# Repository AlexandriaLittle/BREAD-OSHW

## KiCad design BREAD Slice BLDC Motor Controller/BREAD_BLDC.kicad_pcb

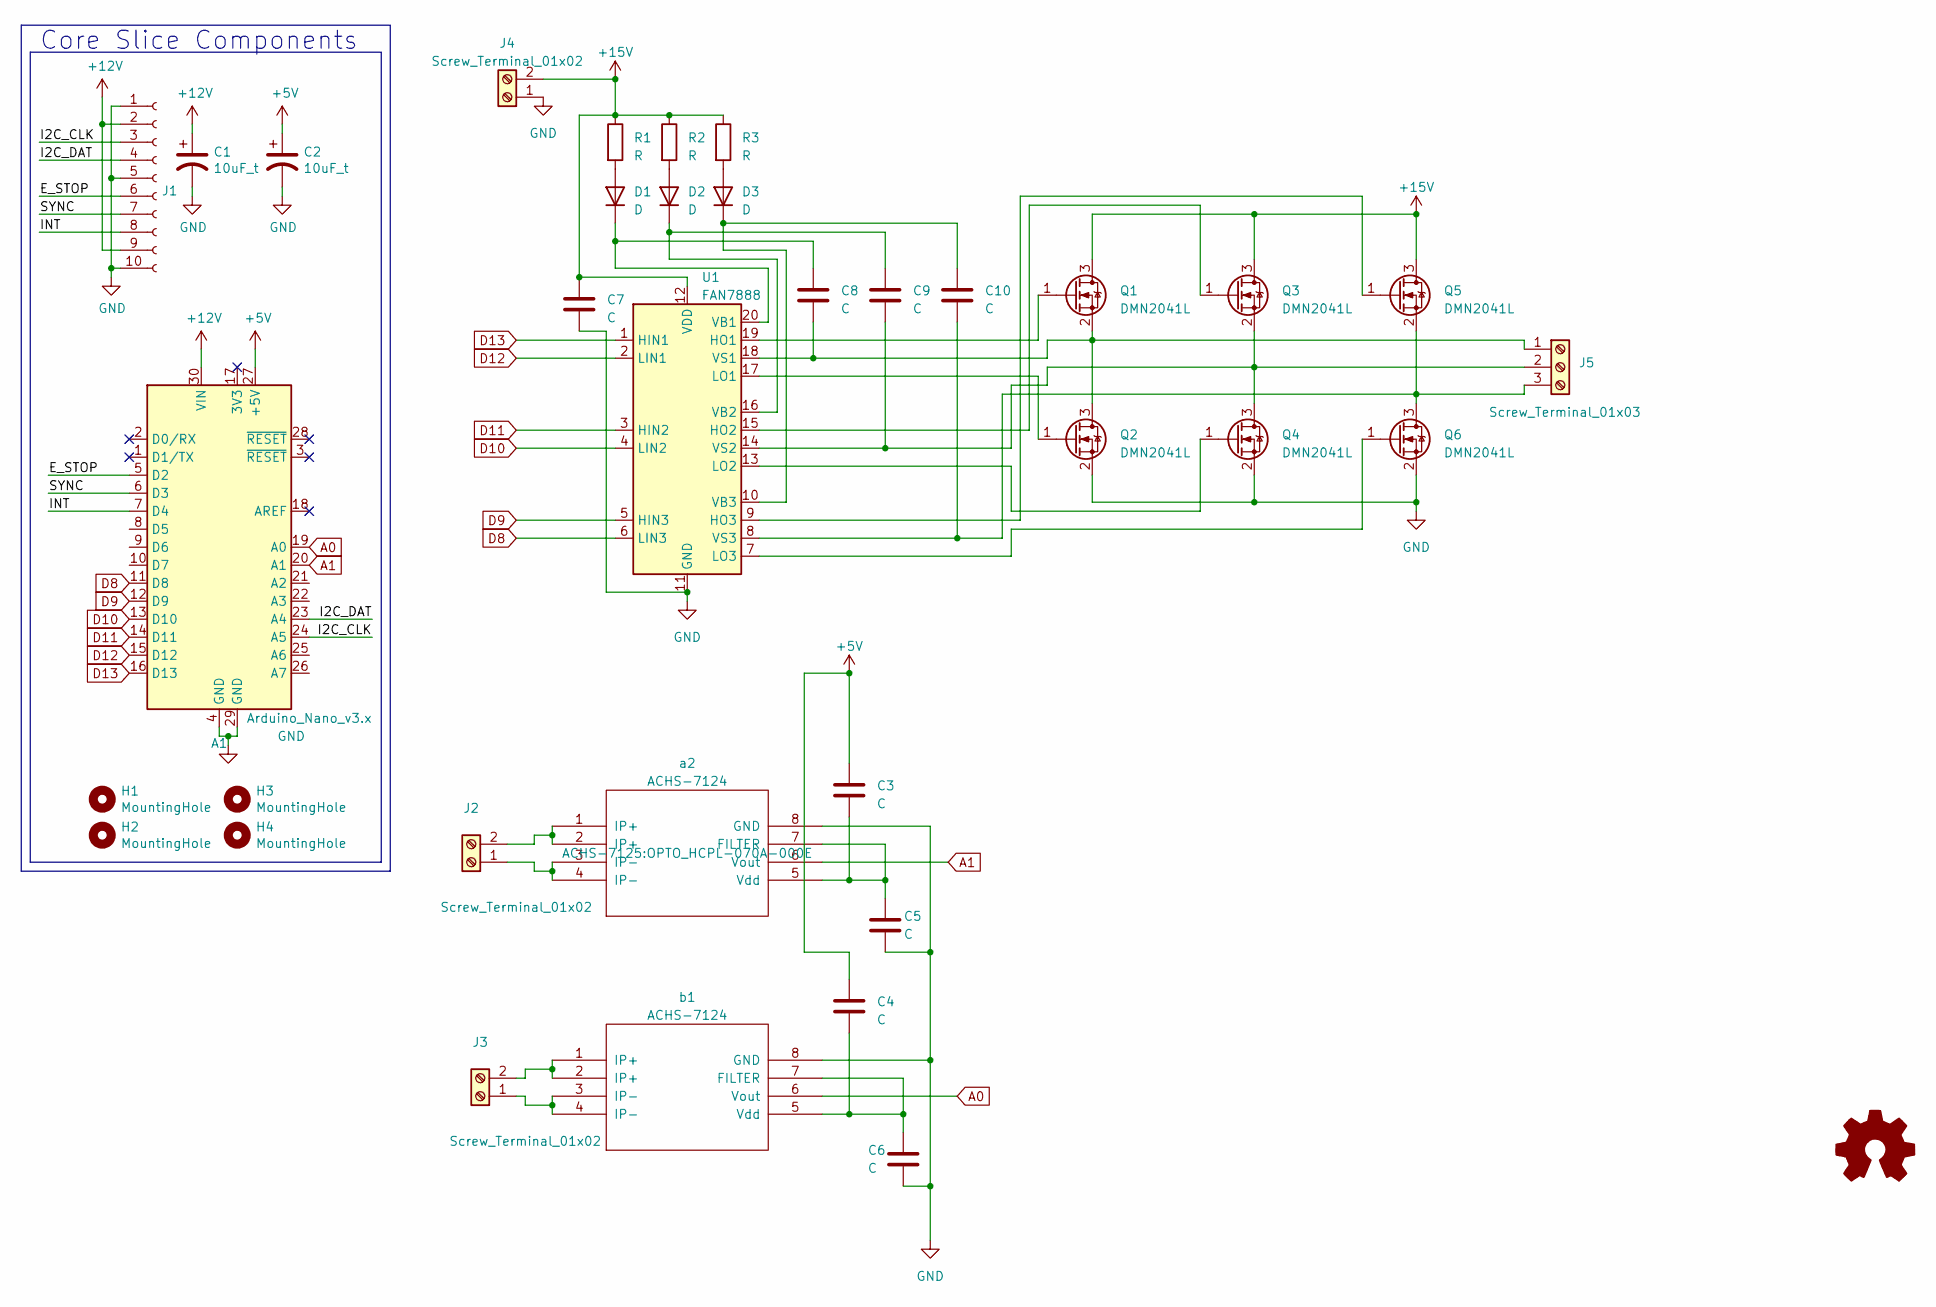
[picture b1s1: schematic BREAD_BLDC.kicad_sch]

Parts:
A1: Arduino_Nano_v3.x; Arduino_Nano
C1, C2: 10uF_t; CP_Radial_D4.0mm_P1.50mm; Part # T491C106K025AT
C3, C4, C5, C6, C7, C8, C9, C10: C; CP_Radial_D4.0mm_P1.50mm
D1, D2, D3: D; D_DO-15_P2.54mm_Vertical_AnodeUp
H1, H2, H3, H4: MountingHole; MountingHole_3.2mm_M3_DIN965_Pad
J1: Conn_01x10_Female; PinSocket_1x10_P2.54mm_Horizontal
J2, J3, J4: Screw_Terminal_01x02; SolderWire-0.127sqmm_1x02_P3.7mm_D0.48mm_OD1mm
J5: Screw_Terminal_01x03; SolderWire-0.127sqmm_1x03_P3.7mm_D0.48mm_OD1mm
Logo1: Logo_Open_Hardware_Small; OSHW-Symbol_6.7x6mm_SilkScreen
Q1, Q2, Q3, Q4, Q5, Q6: DMN2041L; SOT-23
R1, R2, R3: R; R_Axial_DIN0204_L3.6mm_D1.6mm_P1.90mm_Vertical
U1: FAN7888; SOIC-20W_7.5x12.8mm_P1.27mm
a2: ACHS-7124; OPTO_HCPL-070A-000E
b1: ACHS-7124; OPTO_HCPL-070A-000E

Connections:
+5V: A1.27 (+5V), C2.1, C3.1, C4.1
+12V: A1.30 (VIN), C1.1, J1.2, J1.9
+15V: C7.1, J4.2, Q1.3 (D), Q3.3 (D), Q5.3 (D), R1.1, R2.1, R3.1, U1.12 (VDD)
/E_STOP: A1.5 (D2), J1.6
/I2C_CLK: A1.24 (A5), J1.3
/I2C_DAT: A1.23 (A4), J1.4
/INT: A1.7 (D4), J1.8
/SYNC: A1.6 (D3), J1.7
A0: A1.19 (A0), b1.6 (Vout)
A1: A1.20 (A1), a2.6 (Vout)
D8: A1.11 (D8), U1.6 (LIN3)
D9: A1.12 (D9), U1.5 (HIN3)
D10: A1.13 (D10), U1.4 (LIN2)
D11: A1.14 (D11), U1.3 (HIN2)
D12: A1.15 (D12), U1.2 (LIN1)
D13: A1.16 (D13), U1.1 (HIN1)
GND: A1.4 (GND), A1.29 (GND), C1.2, C2.2, C5.2, C6.2, C7.2, J1.1, J1.5, J1.10, J4.1, Q2.2 (S), Q4.2 (S), Q6.2 (S), U1.11 (GND), a2.8 (GND), b1.8 (GND)
unnamed: D1.2 (A), R1.2
unnamed: C8.1, D1.1 (K), U1.20 (VB1)
unnamed: D2.2 (A), R2.2
unnamed: C9.1, D2.1 (K), U1.16 (VB2)
unnamed: D3.2 (A), R3.2
unnamed: C10.1, D3.1 (K), U1.10 (VB3)
unnamed: J2.1, a2.3 (IP-), a2.4 (IP-)
unnamed: J2.2, a2.1 (IP+), a2.2 (IP+)
unnamed: J3.1, b1.3 (IP-), b1.4 (IP-)
unnamed: J3.2, b1.1 (IP+), b1.2 (IP+)
unnamed: C8.2, J5.1, Q1.2 (S), Q2.3 (D), U1.18 (VS1)
unnamed: C9.2, J5.2, Q3.2 (S), Q4.3 (D), U1.14 (VS2)
unnamed: C10.2, J5.3, Q5.2 (S), Q6.3 (D), U1.8 (VS3)
unnamed: Q1.1 (G), U1.19 (HO1)
unnamed: Q2.1 (G), U1.17 (LO1)
unnamed: Q3.1 (G), U1.15 (HO2)
unnamed: Q4.1 (G), U1.13 (LO2)
unnamed: Q5.1 (G), U1.9 (HO3)
unnamed: Q6.1 (G), U1.7 (LO3)
unnamed: C3.2, C5.1, a2.5 (Vdd), a2.7 (FILTER)
unnamed: C4.2, C6.1, b1.5 (Vdd), b1.7 (FILTER)

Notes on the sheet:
Core Slice Components

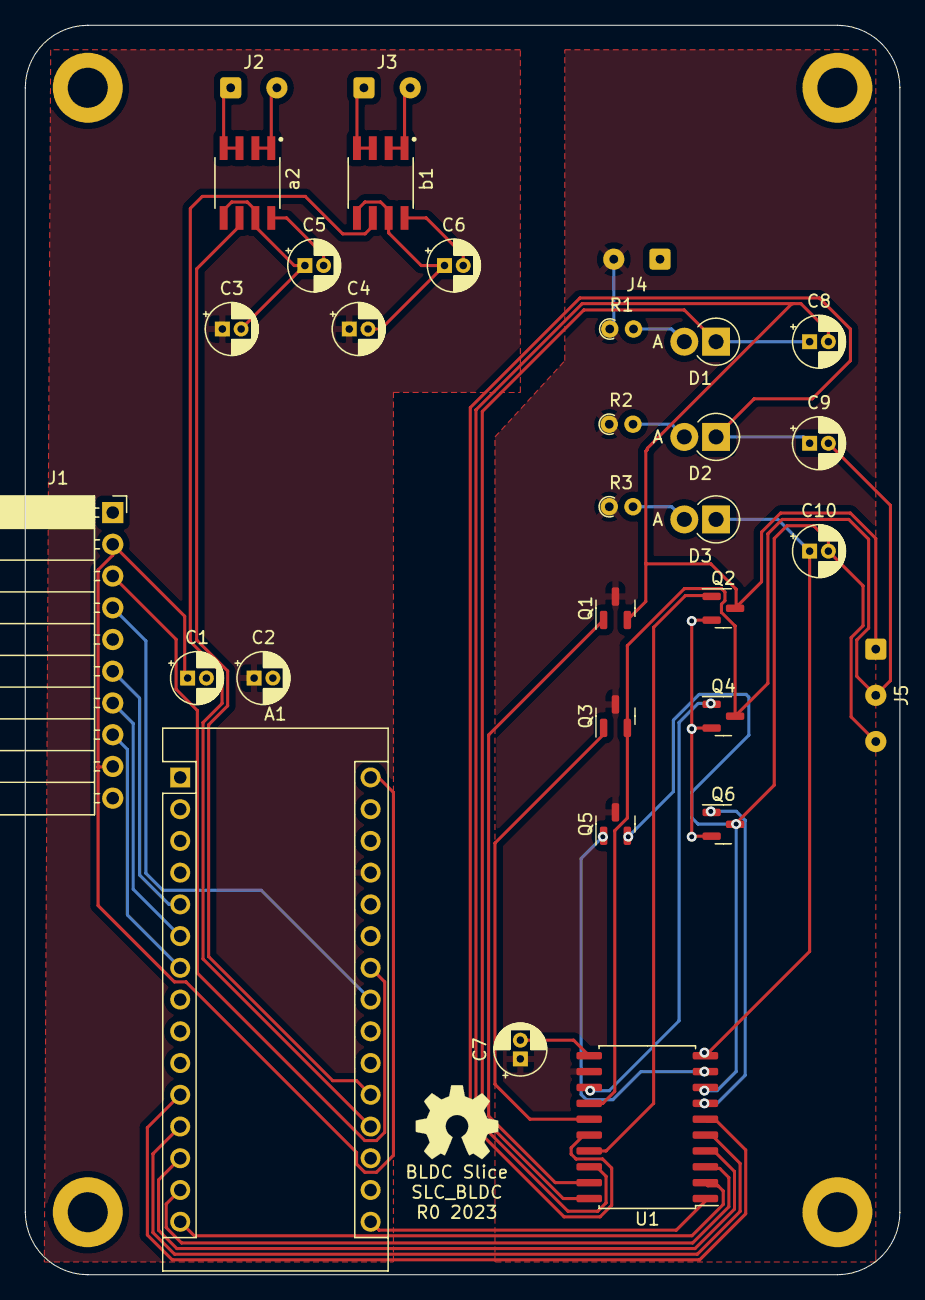
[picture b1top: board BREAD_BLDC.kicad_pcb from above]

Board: 2 copper layers, 70.0 x 100.0 mm, 36 parts (0 on the bottom side), 38 nets.

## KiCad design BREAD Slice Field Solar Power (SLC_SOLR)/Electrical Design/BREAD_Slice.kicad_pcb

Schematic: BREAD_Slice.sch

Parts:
A1: Arduino_Nano_v3.x; Arduino_Nano
C1, C2, C5, C6: 10uF_t; C_2312; Part # T491C106K025AT
C3: 1000 uF; C_2312; Part # T491C106K025AT
C4: 4700 uF; C_2312; Part # T491C106K025AT
D1, D2, D3: LED; LED-5MM
D4: D_Schottky; D_A-405_P7.62mm_Horizontal
H1, H2, H3, H4: MountingHole; MountingHole_3.2mm_M3_DIN965_Pad
J1: Conn_01x10_Female; PinSocket_1x10_P2.54mm_Horizontal
J2, J3: Screw_Terminal_01x02; TerminalBlock_TE_282834-2_1x02_P2.54mm_Horizontal
L1: 100 uH; L_Radial_D12.0mm_P10.00mm_Neosid_SD12k_style1
Logo1: Logo_Open_Hardware_Small; OSHW-Symbol_6.7x6mm_SilkScreen
R1, R2, R3, R9: 1k; R_1206_HandSoldering
R4: 5k; R_1206_HandSoldering
R5: 1.2k; R_1206_HandSoldering
R6, R8: 100k; R_1206_HandSoldering
R7: 2k; R_1206_HandSoldering
RV1: 500k; Potentiometer_Bourns_3296W_Vertical
TH1: 10k; R_Box_L13.0mm_W4.0mm_P9.00mm
TP1, TP2: TestPoint; TestPoint_Loop_D2.54mm_Drill1.5mm_Beaded
U1: LM2576HVT-ADJ; TO-220-5_Vertical
U2: MCP73871; QFN-20-1EP_4x4mm_P0.5mm_EP2.5x2.5mm

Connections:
+5V: A1.27 (+5V), C2.1
/CHG: A1.8 (D5), D1.1 (K), U2.8 (STAT1/~LBO~)
/DONE: A1.9 (D6), D2.1 (K), U2.7 (STAT2)
/E_STOP: A1.5 (D2), J1.6
/I2C_CLK: A1.24 (A5), J1.3
/I2C_DAT: A1.23 (A4), J1.4
/INT: A1.6 (D3), J1.7
/PG: A1.10 (D7), D3.1 (K), U2.6 (~PG~)
/PWR: A1.30 (VIN), C1.1, C5.1, J1.2, J1.9, U2.1 (OUT), U2.20 (OUT)
/SYNC: A1.7 (D4), J1.8
GND: A1.4 (GND), A1.29 (GND), C1.2, C2.2, C3.2, C4.2, C5.2, C6.2, D4.2 (A), J1.1, J1.5, J1.10, J2.2, J3.2, R5.1, R6.1, R7.2, R8.2, RV1.3, TH1.1, TP1.1, U1.3 (GND), U1.5 (~ON~/OFF), U2.10 (VSS), U2.11 (VSS), U2.21 (VSS)
unnamed: C4.1, J2.1, U1.1 (VIN)
unnamed: C6.1, J3.1, U2.14 (VBAT), U2.15 (VBAT), U2.16 (Vbat_SENSE)
unnamed: D1.2 (A), R1.1
unnamed: D2.2 (A), R2.1
unnamed: D3.2 (A), R3.1
unnamed: D4.1 (K), L1.2, U1.2 (OUT)
unnamed: R4.1, R5.2, U1.4 (FB)
unnamed: R6.2, R9.2, TH1.2
unnamed: R7.1, U2.13 (PROG1)
unnamed: R8.1, U2.12 (PROG3)
unnamed: R9.1, U2.5 (THERM)
unnamed: RV1.2, TP2.1, U2.2 (VPCC)
VCC: C3.1, L1.1, R1.2, R2.2, R3.2, R4.2, RV1.1, U2.3 (SEL), U2.4 (PROG2), U2.9 (~TE), U2.17 (CE), U2.18 (IN), U2.19 (IN)

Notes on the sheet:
Core Slice Components

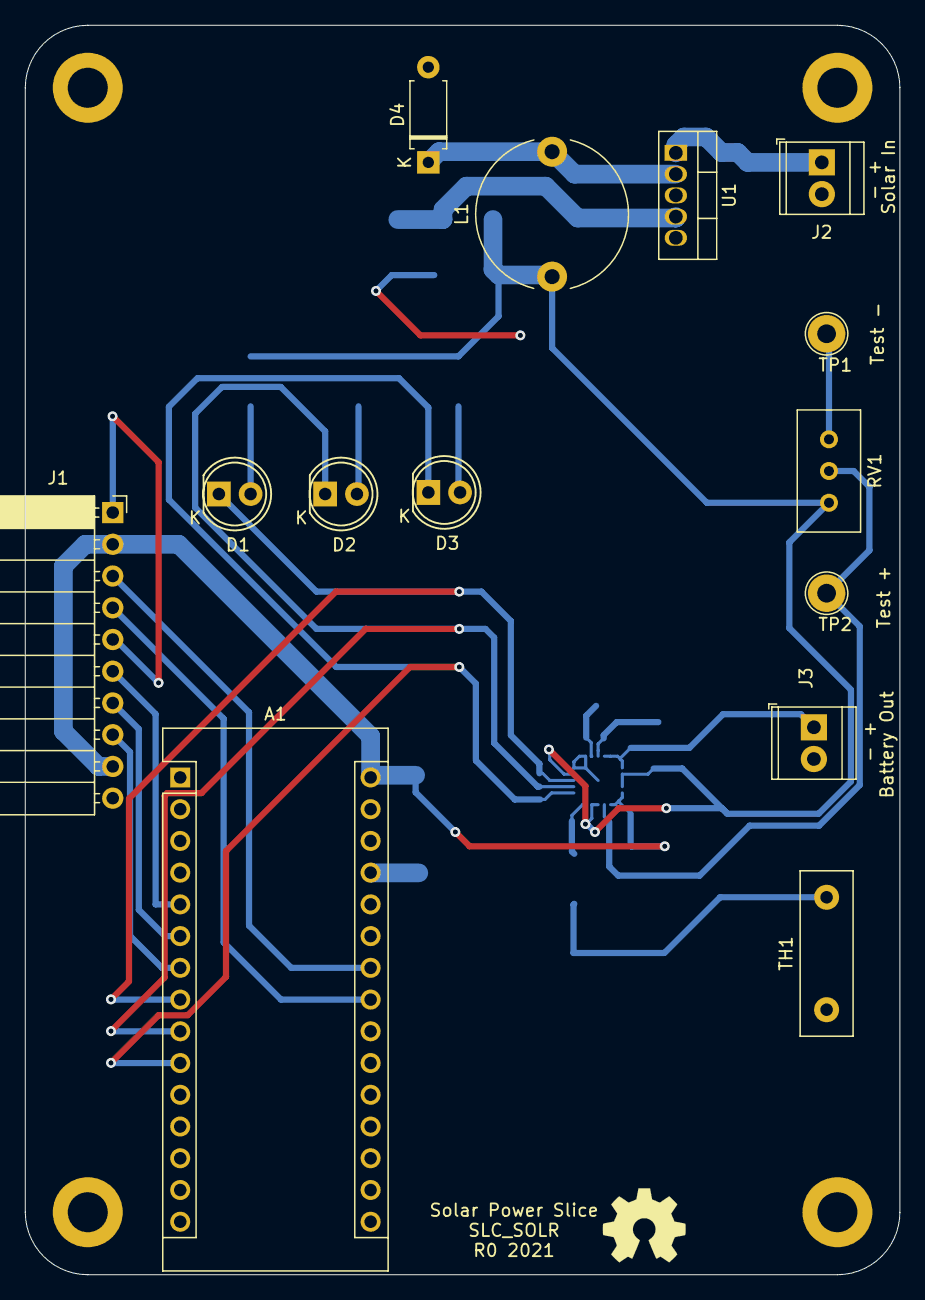
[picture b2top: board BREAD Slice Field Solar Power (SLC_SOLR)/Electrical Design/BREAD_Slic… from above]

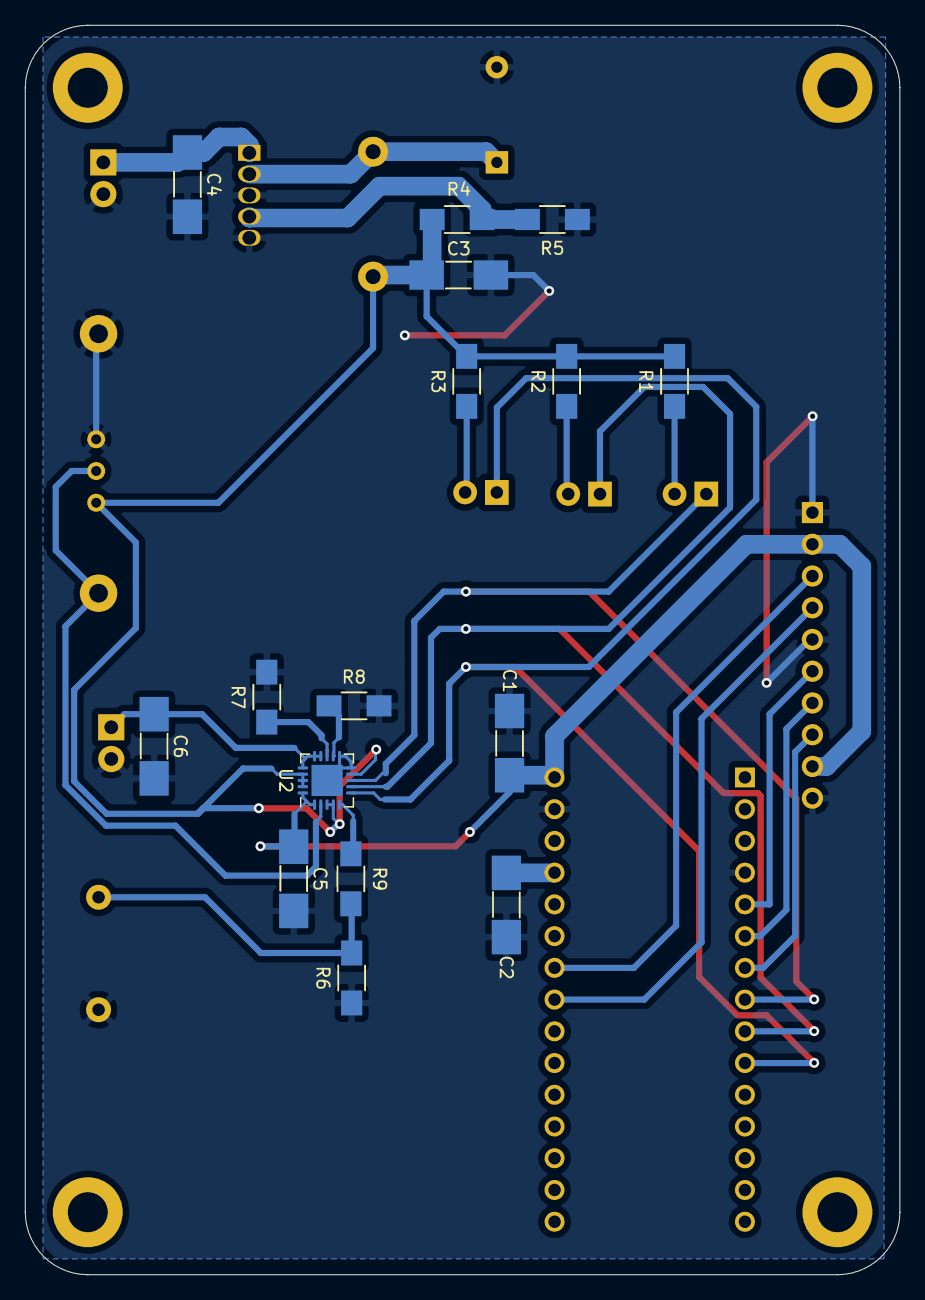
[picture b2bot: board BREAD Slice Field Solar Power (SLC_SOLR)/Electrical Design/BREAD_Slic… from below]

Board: 2 copper layers, 70.0 x 100.0 mm, 35 parts (16 on the bottom side), 24 nets.

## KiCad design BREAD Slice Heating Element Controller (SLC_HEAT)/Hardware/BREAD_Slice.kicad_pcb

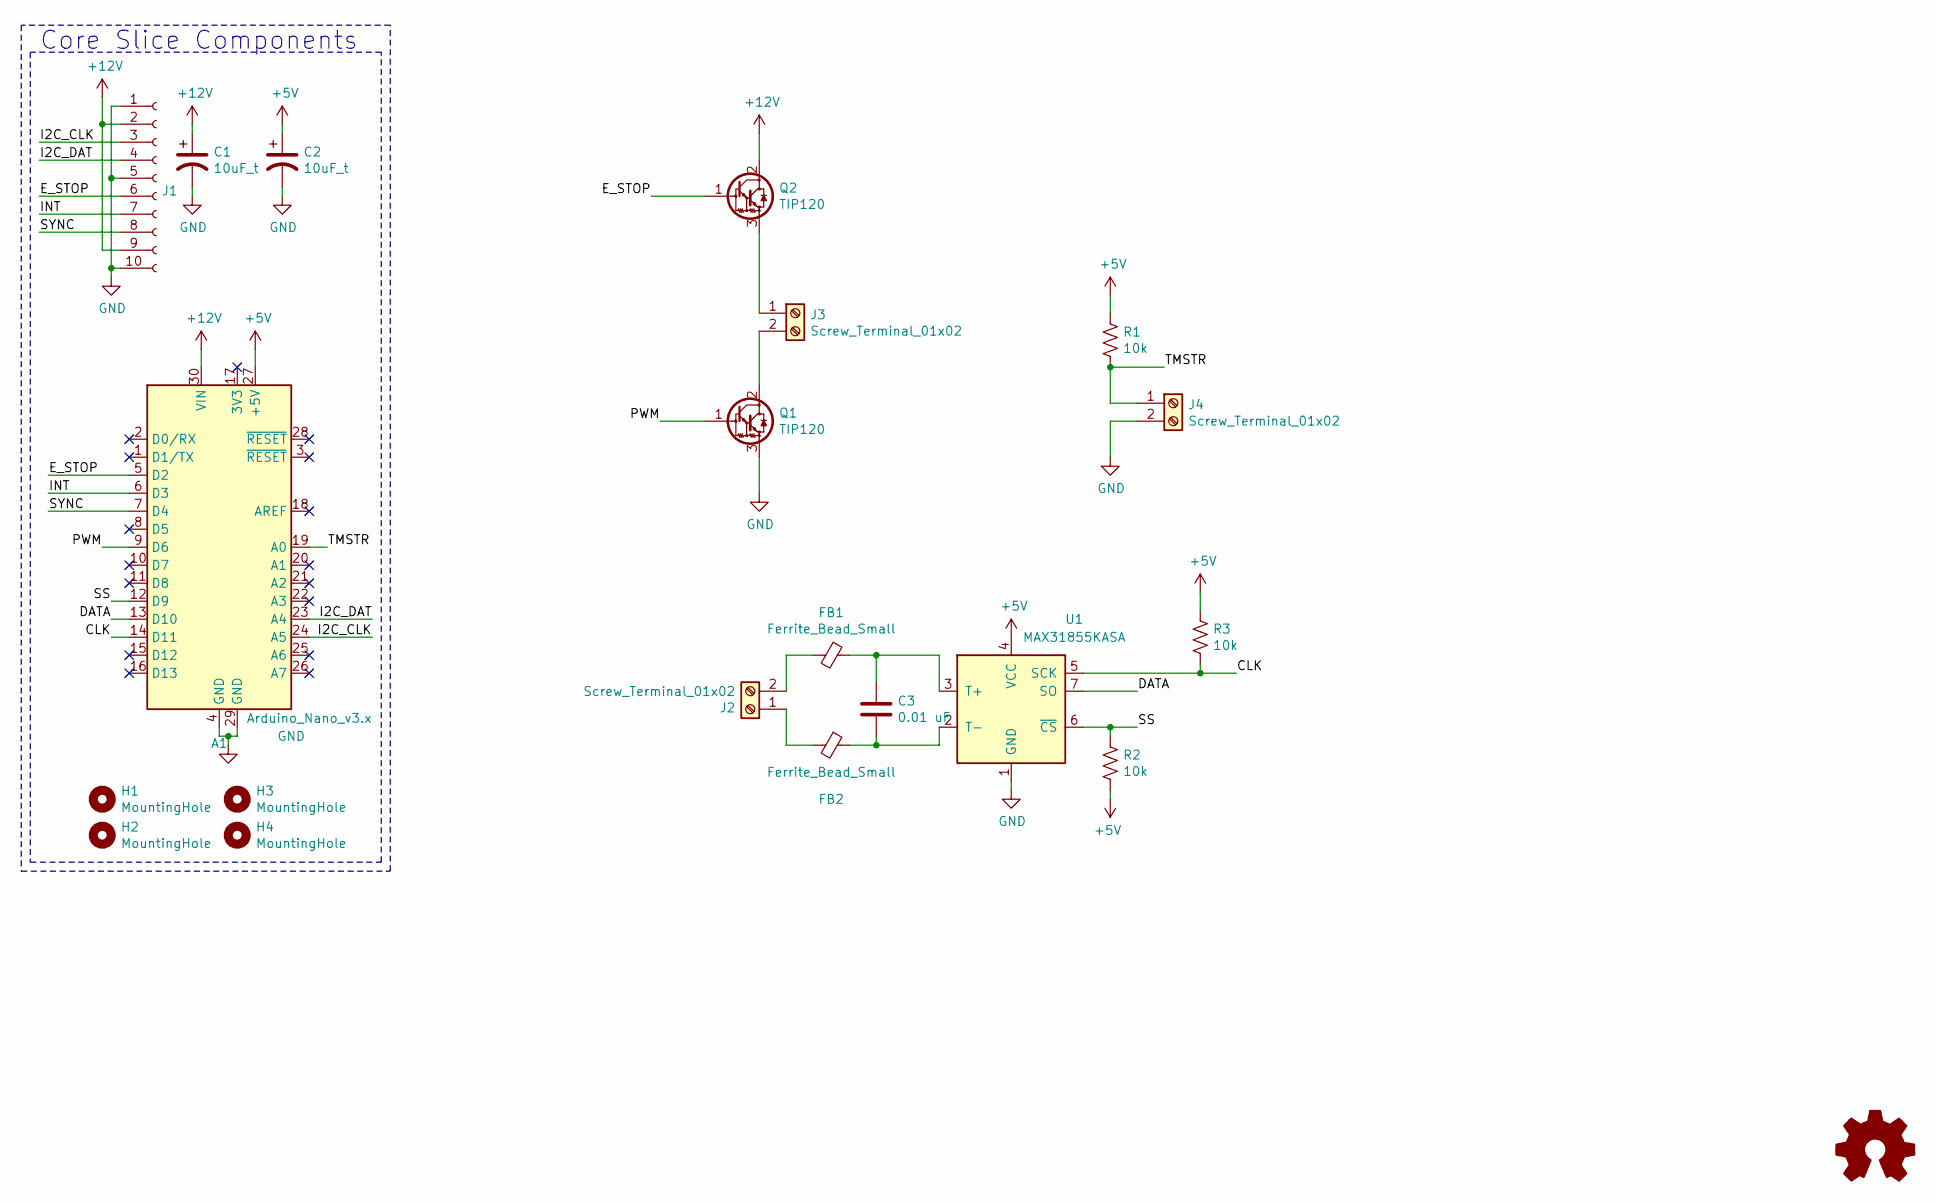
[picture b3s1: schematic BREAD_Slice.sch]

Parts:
A1: Arduino_Nano_v3.x; Arduino_Nano
C1, C2: 10uF_t; C_2312; Part # T491C106K025AT
C3: 0.01 uF; C_1206_HandSoldering
FB1, FB2: Ferrite_Bead_Small; R_1206_HandSoldering
H1, H2, H3, H4: MountingHole; MountingHole_3.2mm_M3_DIN965_Pad
J1: Conn_01x10_Female; PinSocket_1x10_P2.54mm_Horizontal
J2, J3, J4: Screw_Terminal_01x02; TerminalBlock_Pheonix_MKDS1.5-2pol
Logo1: Logo_Open_Hardware_Small; OSHW-Symbol_6.7x6mm_SilkScreen
Q1, Q2: TIP120; TO-220-3_Vertical
R1, R2, R3: 10k; R_1206_HandSoldering
U1: MAX31855KASA; SOIC-8_3.9x4.9mm_P1.27mm

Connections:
+5V: A1.27 (+5V), C2.1, R1.1, R2.2, R3.1, U1.4 (VCC)
+12V: A1.30 (VIN), C1.1, J1.2, J1.9, Q2.2 (C)
/CLK: A1.14 (D11), R3.2, U1.5 (SCK)
/DATA: A1.13 (D10), U1.7 (SO)
/E_STOP: A1.5 (D2), J1.6, Q2.1 (B)
/I2C_CLK: A1.24 (A5), J1.3
/I2C_DAT: A1.23 (A4), J1.4
/INT: A1.6 (D3), J1.7
/PWM: A1.9 (D6), Q1.1 (B)
/SS: A1.12 (D9), R2.1, U1.6 (~CS~)
/SYNC: A1.7 (D4), J1.8
/TMSTR: A1.19 (A0), J4.1, R1.2
GND: A1.4 (GND), A1.29 (GND), C1.2, C2.2, J1.1, J1.5, J1.10, J4.2, Q1.3 (E), U1.1 (GND)
unnamed: C3.1, FB1.1, U1.3 (T+)
unnamed: C3.2, FB2.1, U1.2 (T-)
unnamed: FB1.2, J2.2
unnamed: FB2.2, J2.1
unnamed: J3.1, Q2.3 (E)
unnamed: J3.2, Q1.2 (C)

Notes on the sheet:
Core Slice Components

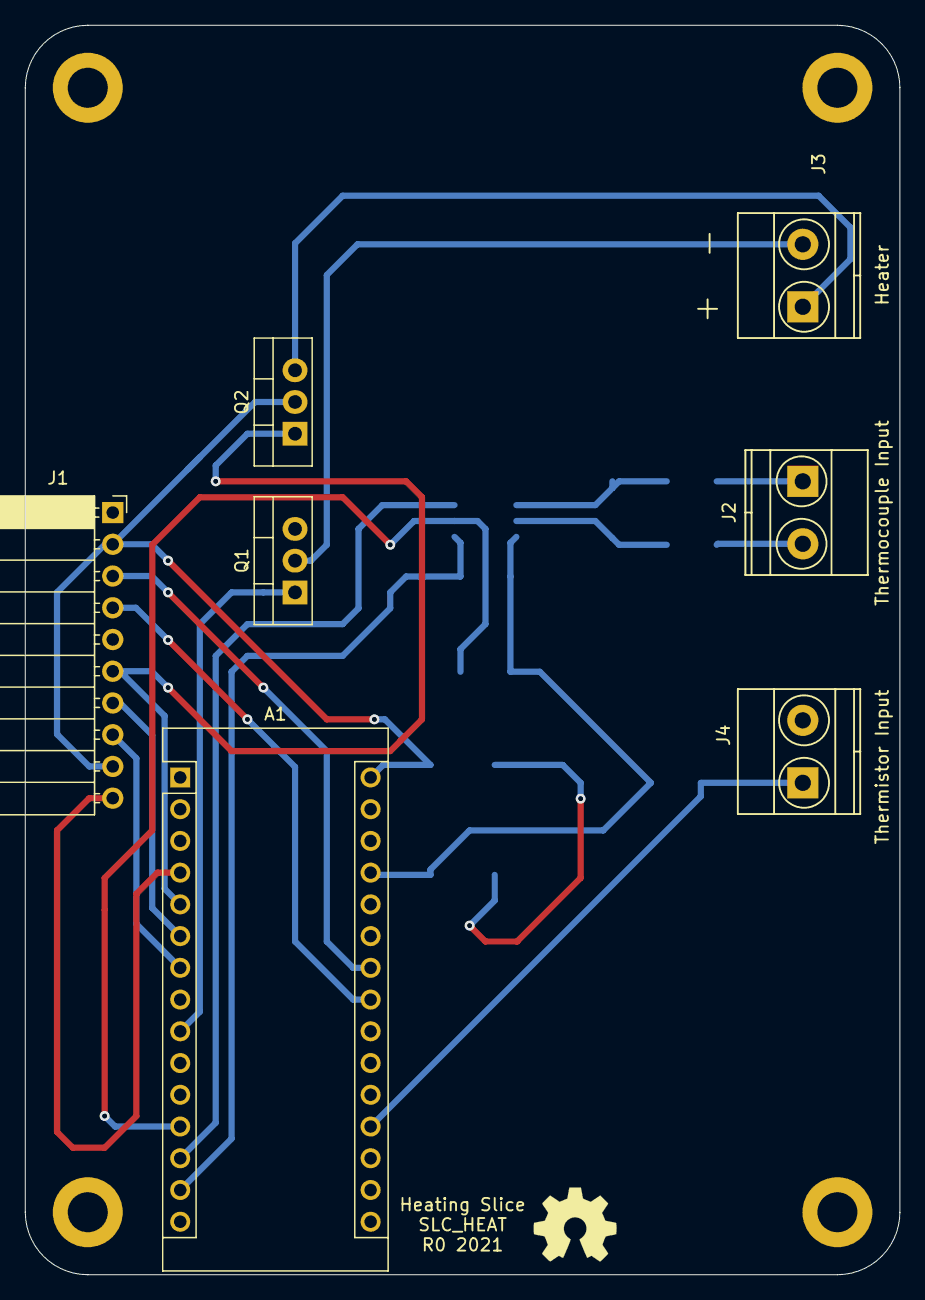
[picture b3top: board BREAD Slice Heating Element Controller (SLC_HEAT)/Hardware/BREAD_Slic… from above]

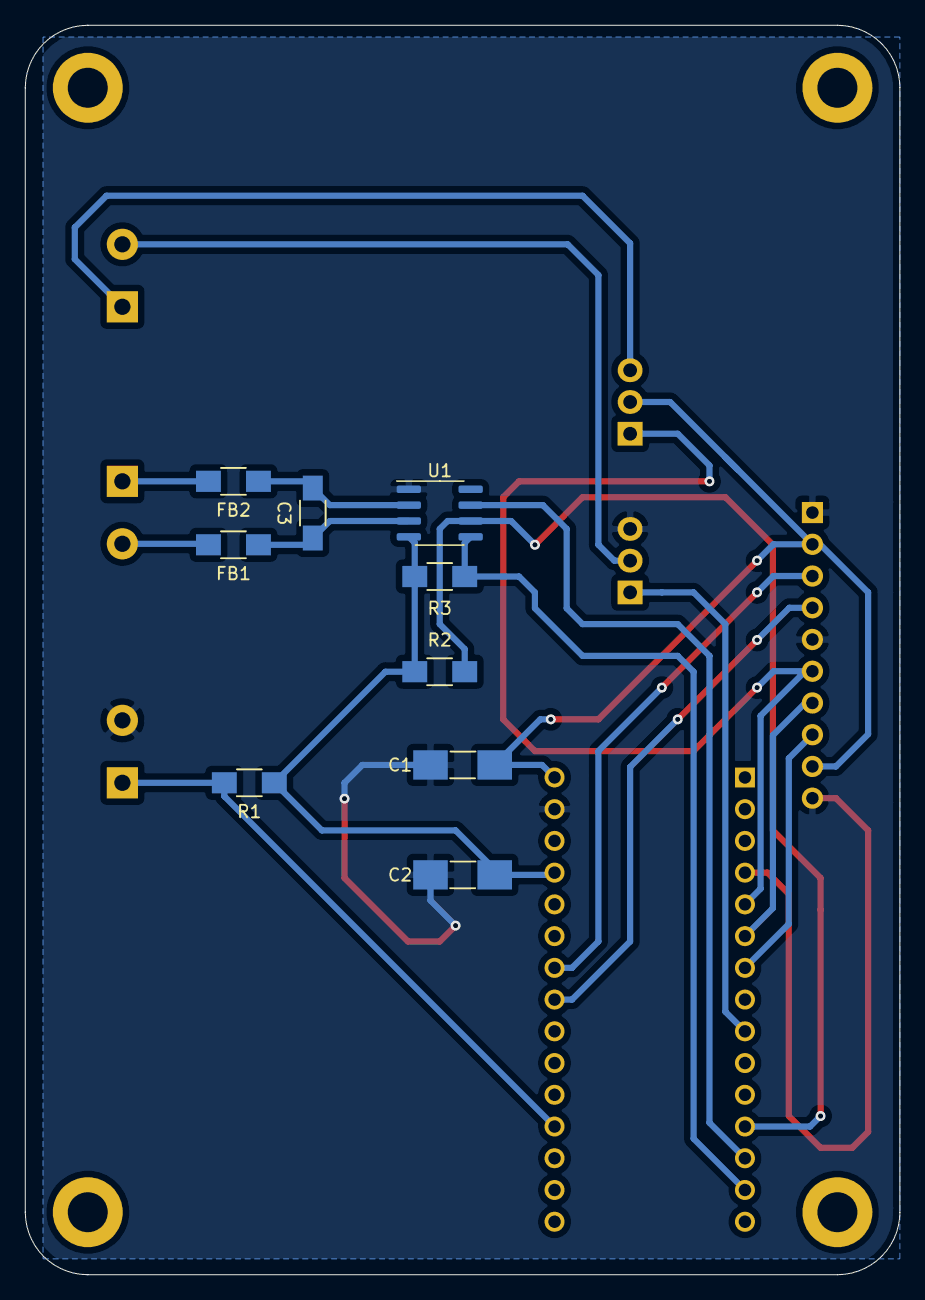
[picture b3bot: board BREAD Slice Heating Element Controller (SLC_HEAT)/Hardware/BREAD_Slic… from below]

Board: 2 copper layers, 70.0 x 100.0 mm, 21 parts (9 on the bottom side), 19 nets.

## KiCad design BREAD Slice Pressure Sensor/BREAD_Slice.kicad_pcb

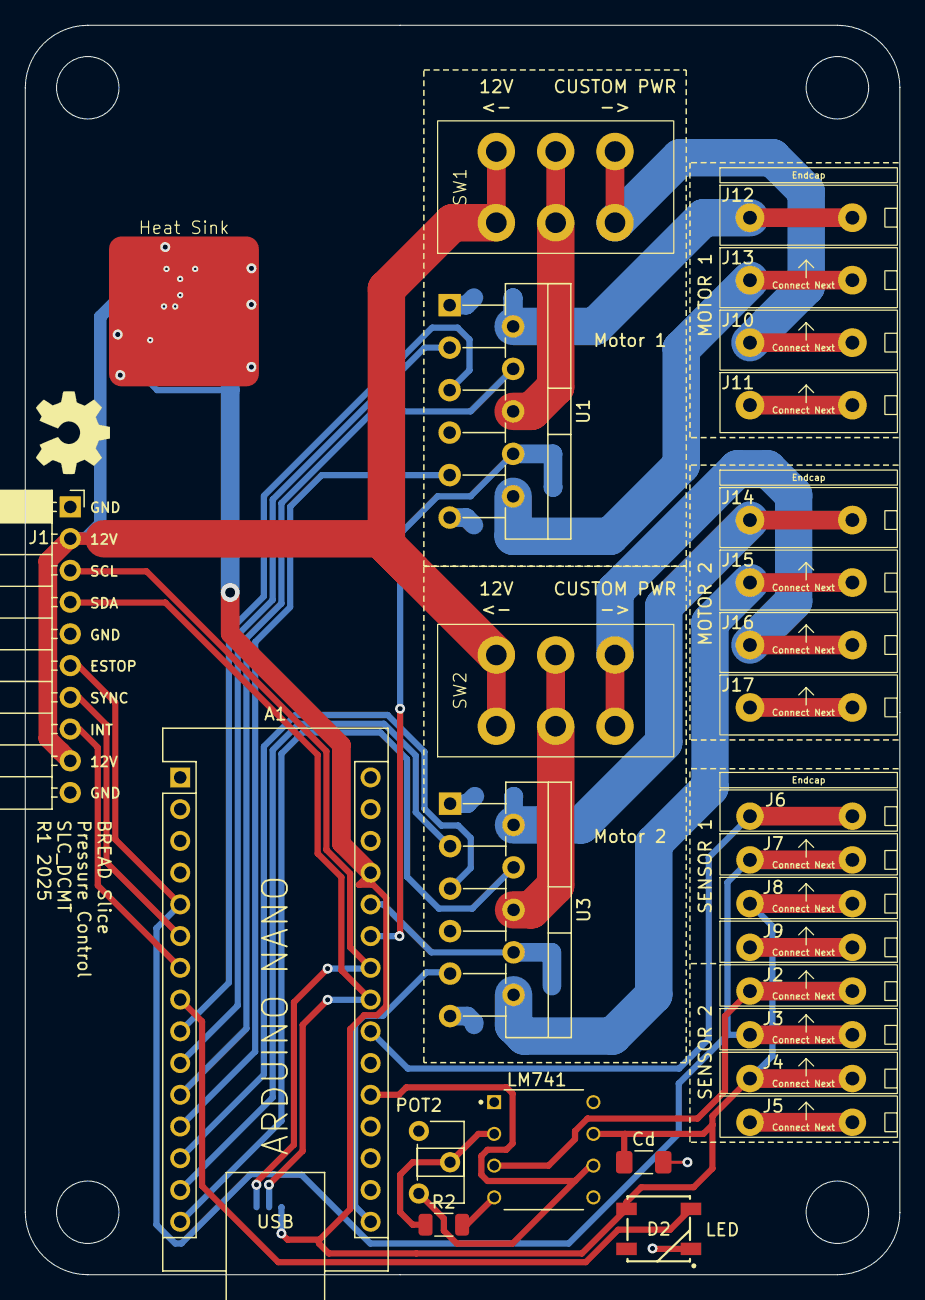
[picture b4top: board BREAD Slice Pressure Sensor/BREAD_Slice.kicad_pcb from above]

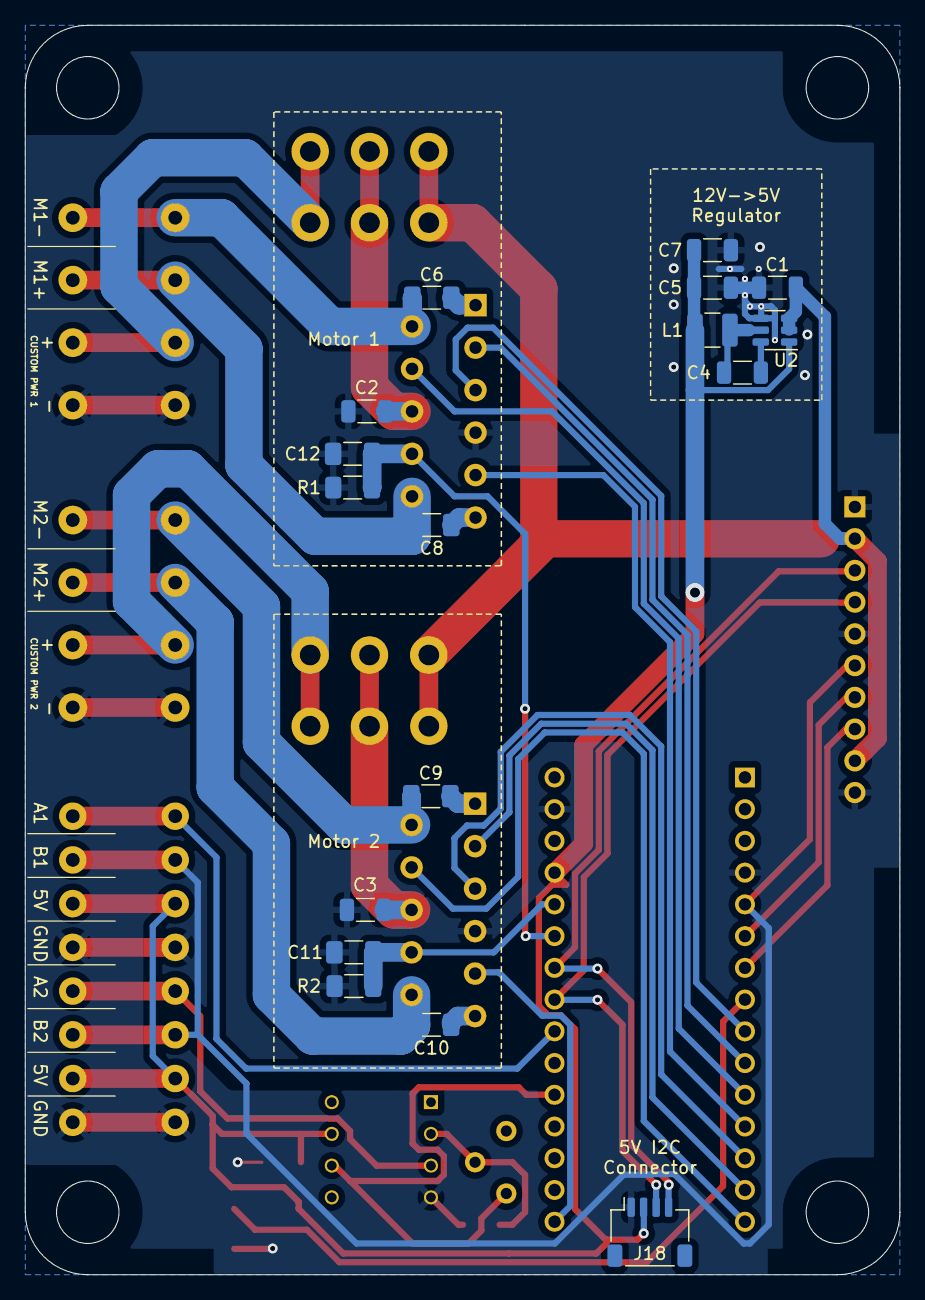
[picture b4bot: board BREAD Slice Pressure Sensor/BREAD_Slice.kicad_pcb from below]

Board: 2 copper layers, 70.0 x 100.0 mm, 50 parts (17 on the bottom side), 35 nets.

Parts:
A1: Arduino_Nano_v3.x; Arduino_Nano
C1, C5, C7: 22uF; C_1206_3216Metric
C2, C3: 10uF_t; C_1206_3216Metric
C4: 100nF; C_1206_3216Metric
C6, C8, C9, C10, C11, C12: 10 nF; C_1206_3216Metric_Pad1.33x1.80mm_HandSolder
Cd: C_1206_3216Metric_Pad1.33x1.80mm_HandSolder
D2: WS2812B_5050; WS2812-5050-4PIN
H1, H2, H3, H4: MountingHole; MountingHole_5mm
HS1: Heatsink_Pad; Thermal Pad
J1: Conn_01x10_Female; PinSocket_1x10_P2.54mm_Horizontal
J2, J3, J4, J5, J7, J8, J9: Term_PressFit_Phoenix_Contact; Term_PressFit_3.5mm_H_PC
J6: Term_PressFit_Phoenix_Contact; Term_PressFit_3.5mm_H_ENDCAP_PC
J10, J11, J13, J15, J16, J17: Term_PressFit_Phoenix_Contact; Term_PressFit_5mm_H_PC
J12, J14: Term_PressFit_Phoenix_Contact; Term_PressFit_5mm_H_ENDCAP_PC
J18: I2C_01x04; JST_SH_SM04B-SRSS-TB_1x04-1MP_P1.00mm_Horizontal
L1: 4.7uH; L_1210_3225Metric
LM741: DIP794W45P254L959H508Q8
Logo1: Logo_Open_Hardware_Small; OSHW-Symbol_6.7x6mm_SilkScreen
POT2: Potentiometer_ACP_CA6-H2,5_Horizontal
R1, R2#2: 4.42 k; R_1206_3216Metric_Pad1.30x1.75mm_HandSolder
R2: R_1206_3216Metric
SW1, SW2: SW_SPDT; L102011MS02Q
U1, U3: LMD18200; TO-220-11_P3.4x5.08mm_StaggerOdd_Lead4.85mm_Vertical
U2: AP63205WU-7; TSOT-23-6

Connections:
+5V: A1.27 (+5V), C5.2, C7.2, Cd.1, D2.1 (VDD), J4.1, J8.1, J18.2, L1.2, LM741.7, U2.1 (FB)
+12V: C1.2, J1.2, J1.9, SW1.1 (A), SW2.1 (A), U2.2 (EN), U2.3 (VIN)
/A1: A1.22 (A3), J6.1
/A2: A1.20 (A1), LM741.6
/BR1: A1.11 (D8), U1.4 (BRAKE)
/BR2: A1.15 (D12), U3.4 (BRAKE)
/CSEN1: A1.25 (A6), C12.1, R1.1, U1.8 (CURRENT_SENSE_OUTPUT)
/CSEN2: A1.26 (A7), C11.1, R2#2.1, U3.8 (CURRENT_SENSE_OUTPUT)
/CUST1: J10.1, SW1.3 (C)
/CUST2: J16.1, SW2.3 (C)
/DIR1: A1.10 (D7), U1.3 (DIRECTION)
/DIR2: A1.14 (D11), U3.3 (DIRECTION)
/E_STOP: A1.5 (D2), J1.6, J3.1, J7.1
/I2C_CLK: A1.24 (A5), J1.3, J18.4
/I2C_DAT: A1.23 (A4), J1.4, J18.3
/INT: A1.6 (D3), J1.7
/LED: A1.8 (D5), D2.4 (DIN)
/MC1: A1.9 (D6), U1.5 (PWM)
/MC2: A1.13 (D10), U3.5 (PWM)
/SYNC: A1.7 (D4), J1.8
/THRM1: A1.12 (D9), U1.9 (~THERMAL_FLAG_OUTPUT)
/THRM2: A1.16 (D13), U3.9 (~THERMAL_FLAG_OUTPUT)
GND: A1.4 (GND), A1.29 (GND), C1.1, C2.2, C3.2, C5.1, C7.1, C11.2, C12.2, Cd.2, D2.3 (VSS), HS1.1, J1.1, J1.5, J1.10, J5.1, J9.1, J11.1, J17.1, J18.1, LM741.4, R1.2, R2.2, R2#2.2, U1.7 (GND), U2.4 (GND), U3.7 (GND)
unnamed: C2.1, SW1.2 (B), U1.6 (VS)
unnamed: C3.1, SW2.2 (B), U3.6 (VS)
unnamed: C6.2, U1.1 (BOOTSTRAP1)
unnamed: C8.1, U1.11 (BOOTSTRAP2)
unnamed: C6.1, J12.1, U1.2 (OUTPUT1)
unnamed: C8.2, J13.1, U1.10 (OUTPUT2)
unnamed: C4.2, U2.6 (BST)
unnamed: C4.1, L1.1, U2.5 (SW)
unnamed: C9.2, U3.1 (BOOTSTRAP1)
unnamed: C10.1, U3.11 (BOOTSTRAP2)
unnamed: C9.1, J14.1, U3.2 (OUTPUT1)
unnamed: C10.2, J15.1, U3.10 (OUTPUT2)

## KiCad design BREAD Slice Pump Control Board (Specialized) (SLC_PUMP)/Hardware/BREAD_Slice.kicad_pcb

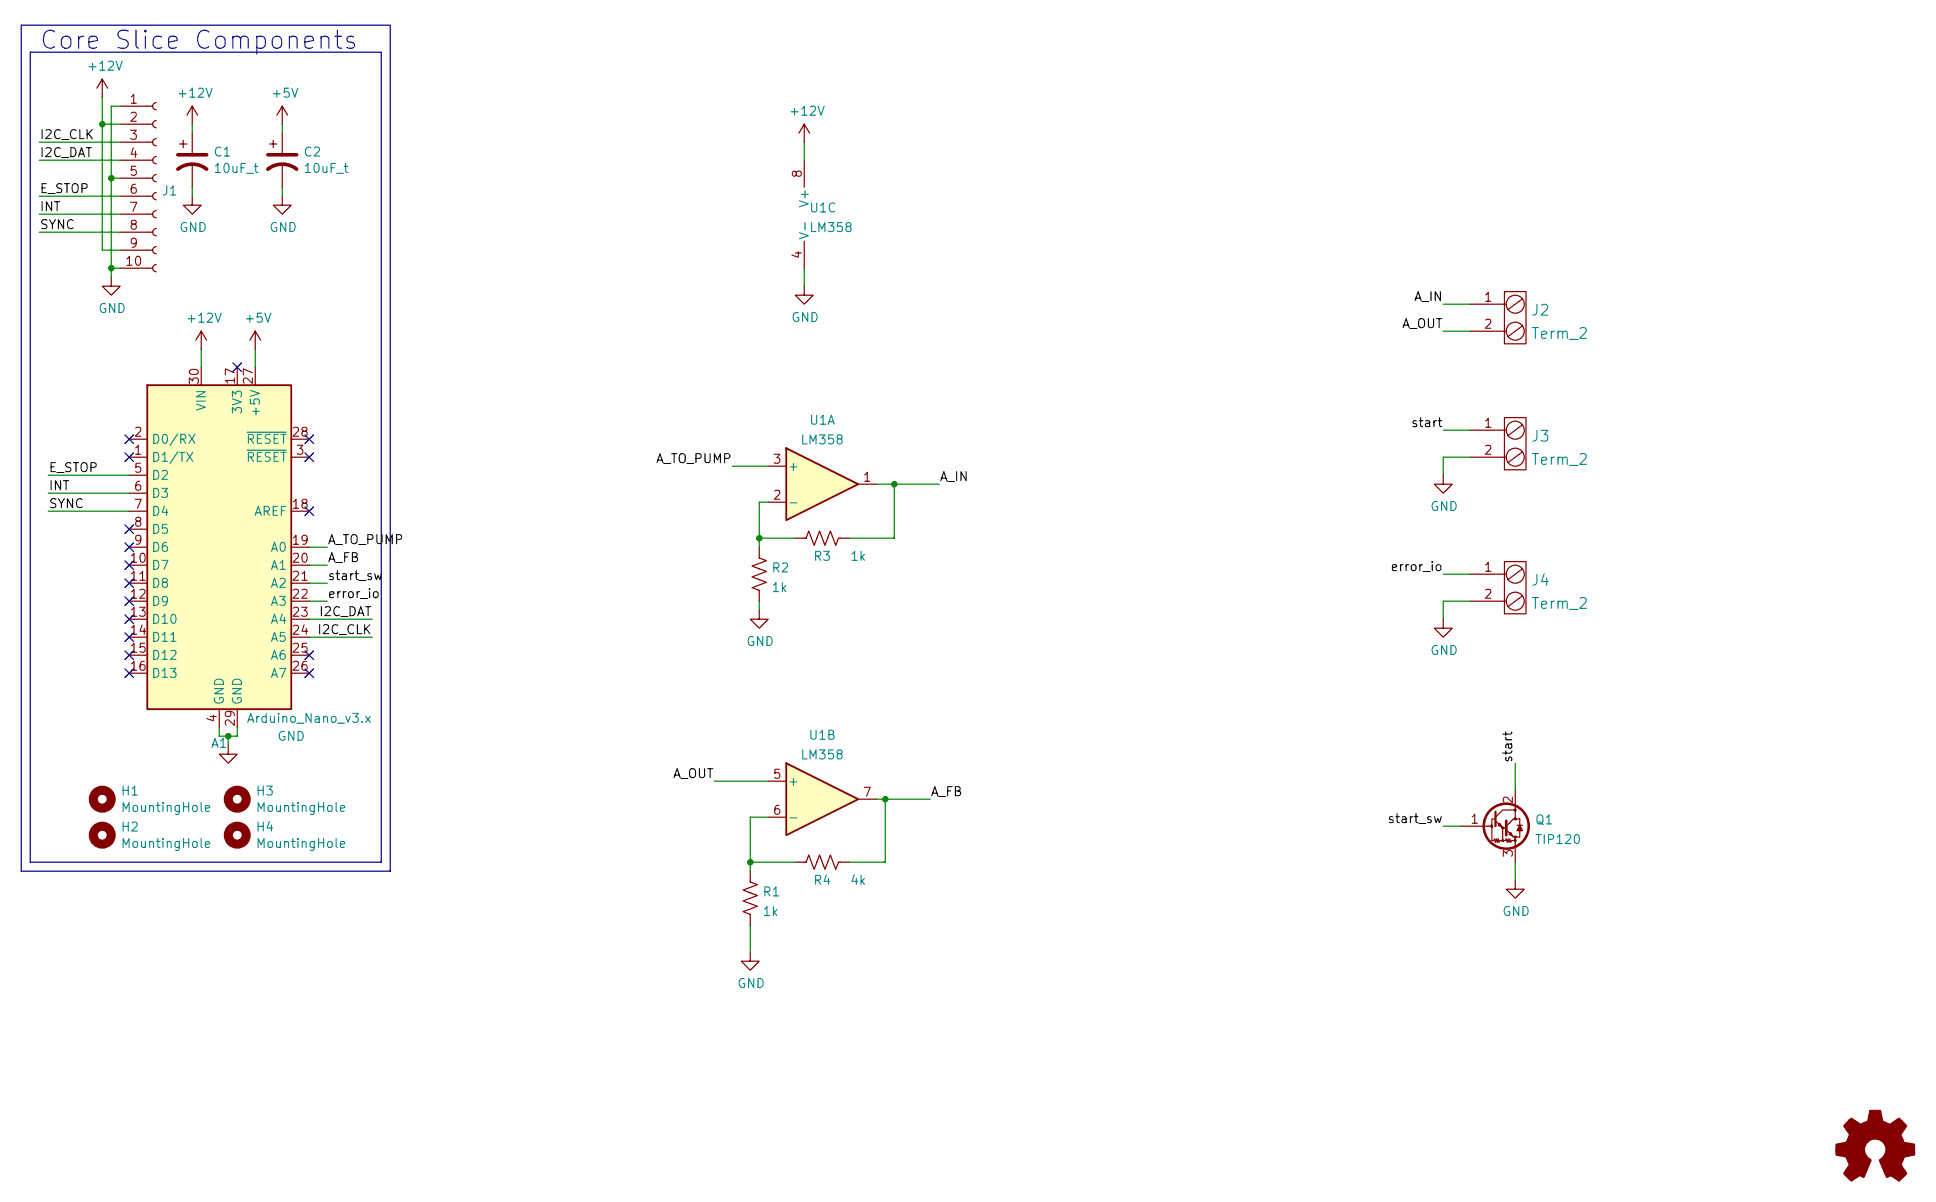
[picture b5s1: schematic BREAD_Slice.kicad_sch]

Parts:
A1: Arduino_Nano_v3.x; Arduino_Nano
C1, C2: 10uF_t; C_2312; Part # T491C106K025AT
H1, H2, H3, H4: MountingHole; MountingHole_3.2mm_M3_DIN965_Pad
J1: Conn_01x10_Female; PinSocket_1x10_P2.54mm_Horizontal
J2, J3, J4: Term_2; TerminalBlock_Pheonix_MKDS1.5-2pol; Part # 1935161
Logo1: Logo_Open_Hardware_Small; OSHW-Symbol_6.7x6mm_SilkScreen
Q1: TIP120; TO-220-3_Vertical
R1, R2, R3: 1k; R_1206_HandSoldering
R4: 4k; R_1206_HandSoldering
U1: LM358

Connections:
+5V: A1.27 (+5V), C2.1
+12V: A1.30 (VIN), C1.1, J1.2, J1.9, U1.8 (V+)
/A_FB: A1.20 (A1), R4.2, U1.7
/A_IN: J2.1, R3.2, U1.1
/A_OUT: J2.2, U1.5 (+)
/A_TO_PUMP: A1.19 (A0), U1.3 (+)
/E_STOP: A1.5 (D2), J1.6
/I2C_CLK: A1.24 (A5), J1.3
/I2C_DAT: A1.23 (A4), J1.4
/INT: A1.6 (D3), J1.7
/SYNC: A1.7 (D4), J1.8
/error_io: A1.22 (A3), J4.1
/start: J3.1, Q1.2 (C)
/start_sw: A1.21 (A2), Q1.1 (B)
GND: A1.4 (GND), A1.29 (GND), C1.2, C2.2, J1.1, J1.5, J1.10, J3.2, J4.2, Q1.3 (E), R1.1, R2.1, U1.4 (V-)
unnamed: R1.2, R4.1, U1.6 (-)
unnamed: R2.2, R3.1, U1.2 (-)

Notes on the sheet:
Core Slice Components
